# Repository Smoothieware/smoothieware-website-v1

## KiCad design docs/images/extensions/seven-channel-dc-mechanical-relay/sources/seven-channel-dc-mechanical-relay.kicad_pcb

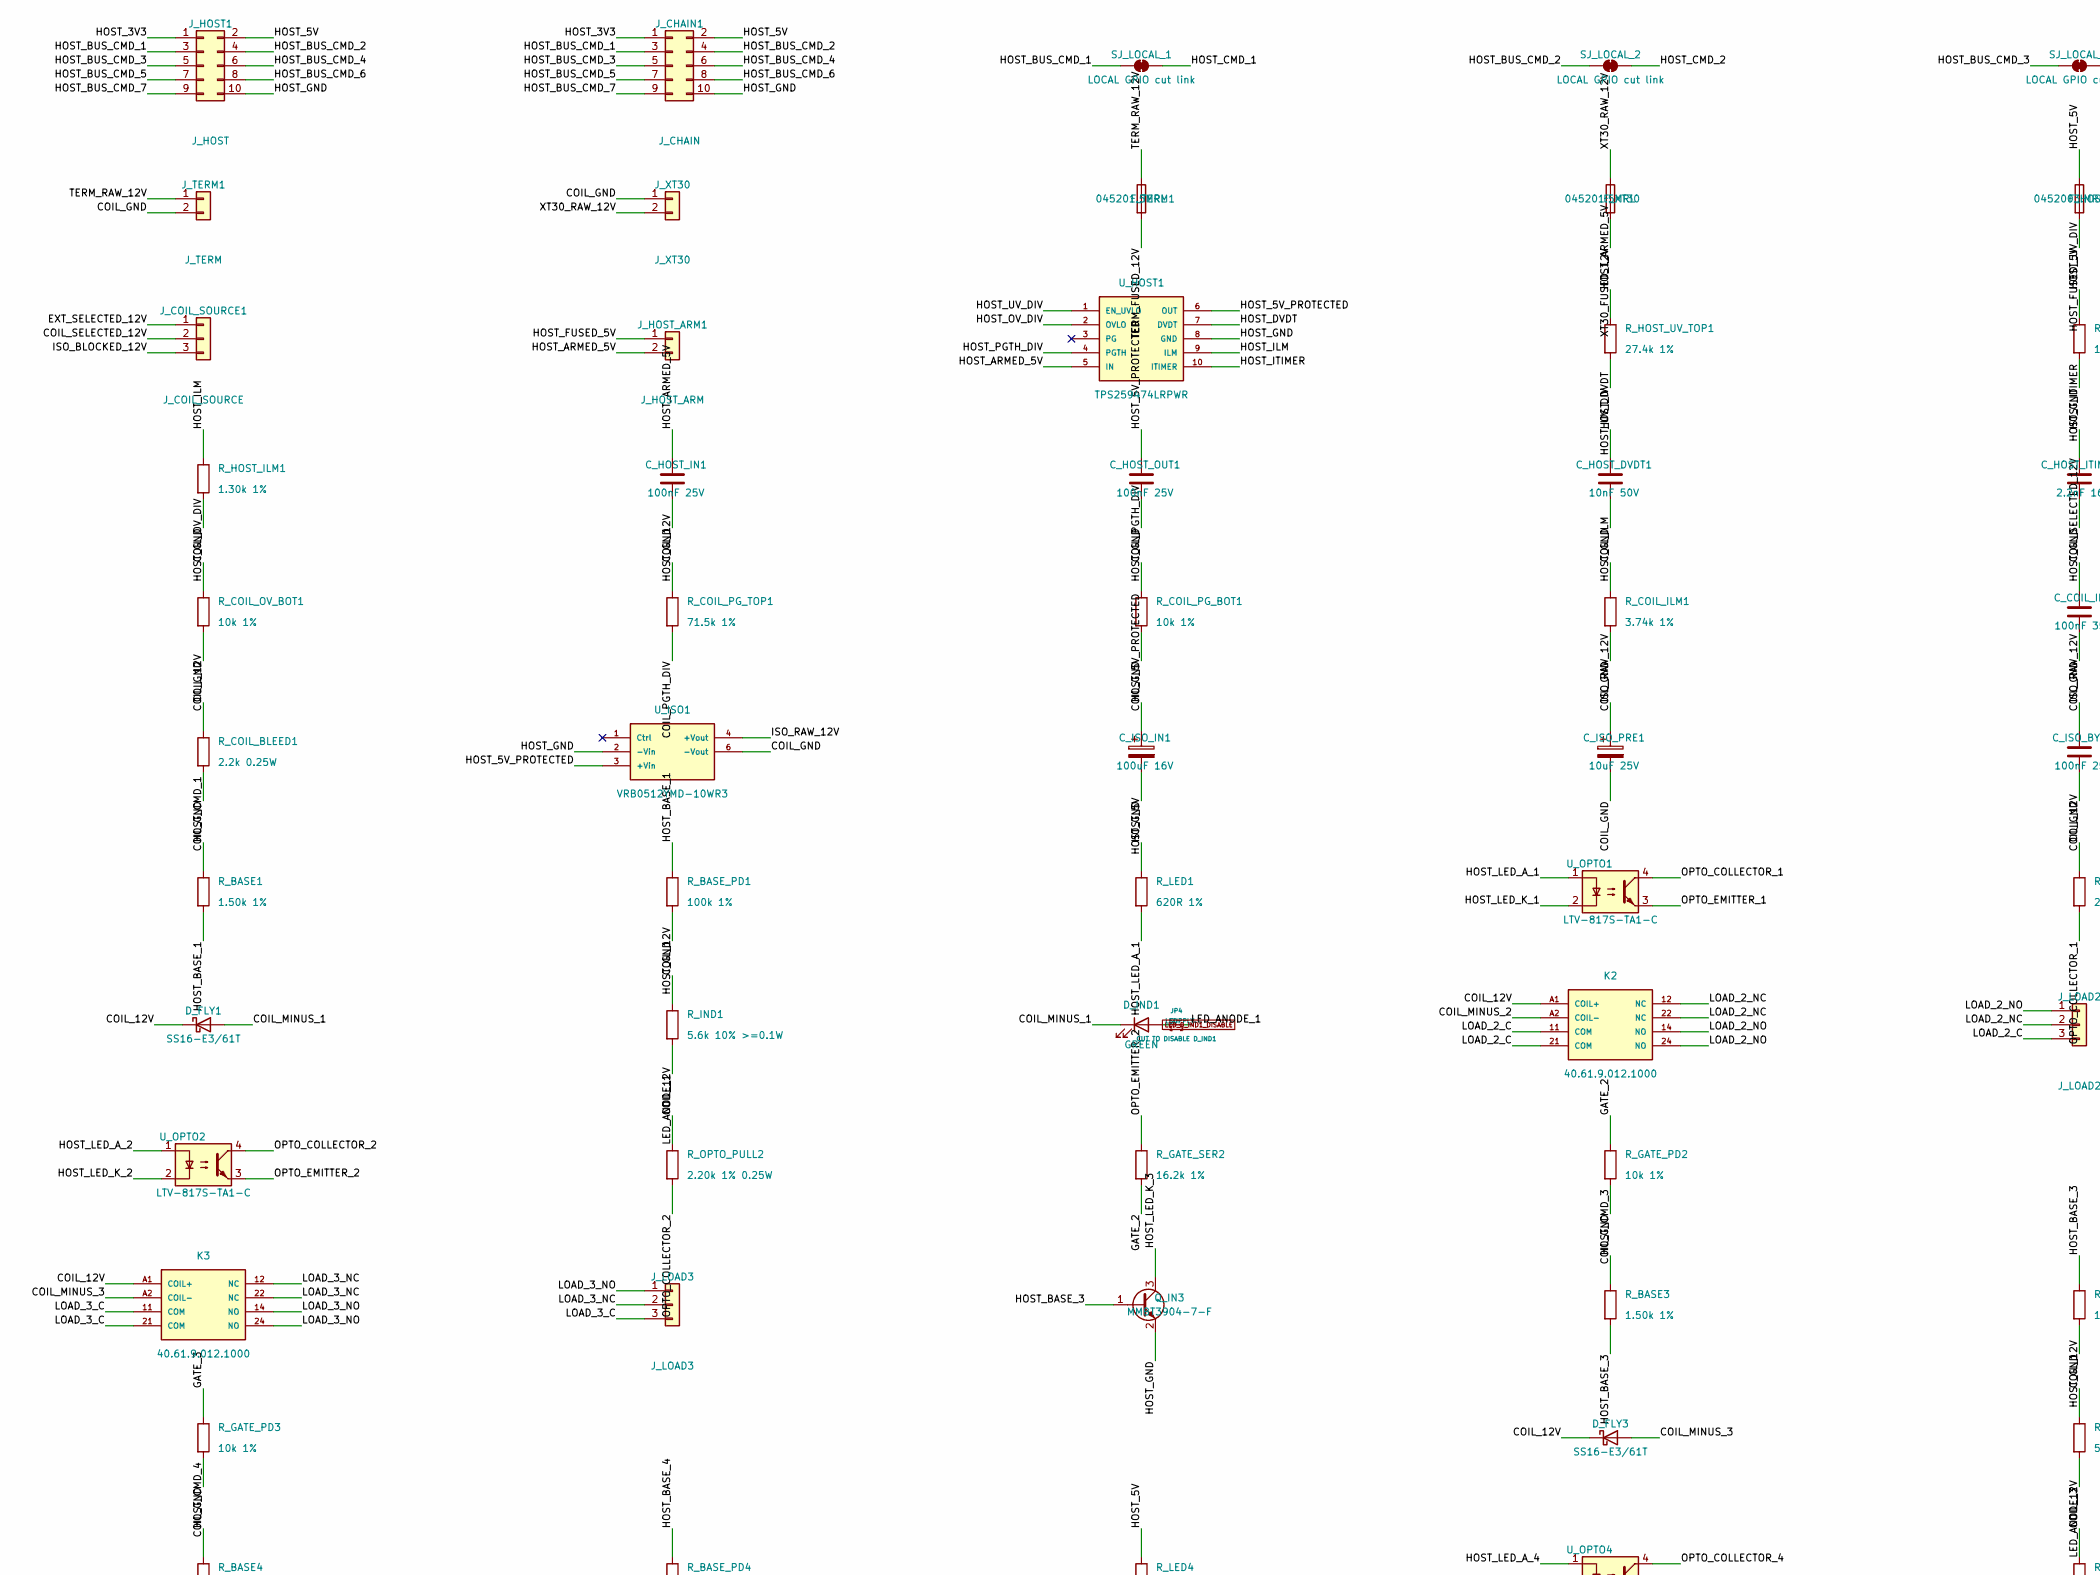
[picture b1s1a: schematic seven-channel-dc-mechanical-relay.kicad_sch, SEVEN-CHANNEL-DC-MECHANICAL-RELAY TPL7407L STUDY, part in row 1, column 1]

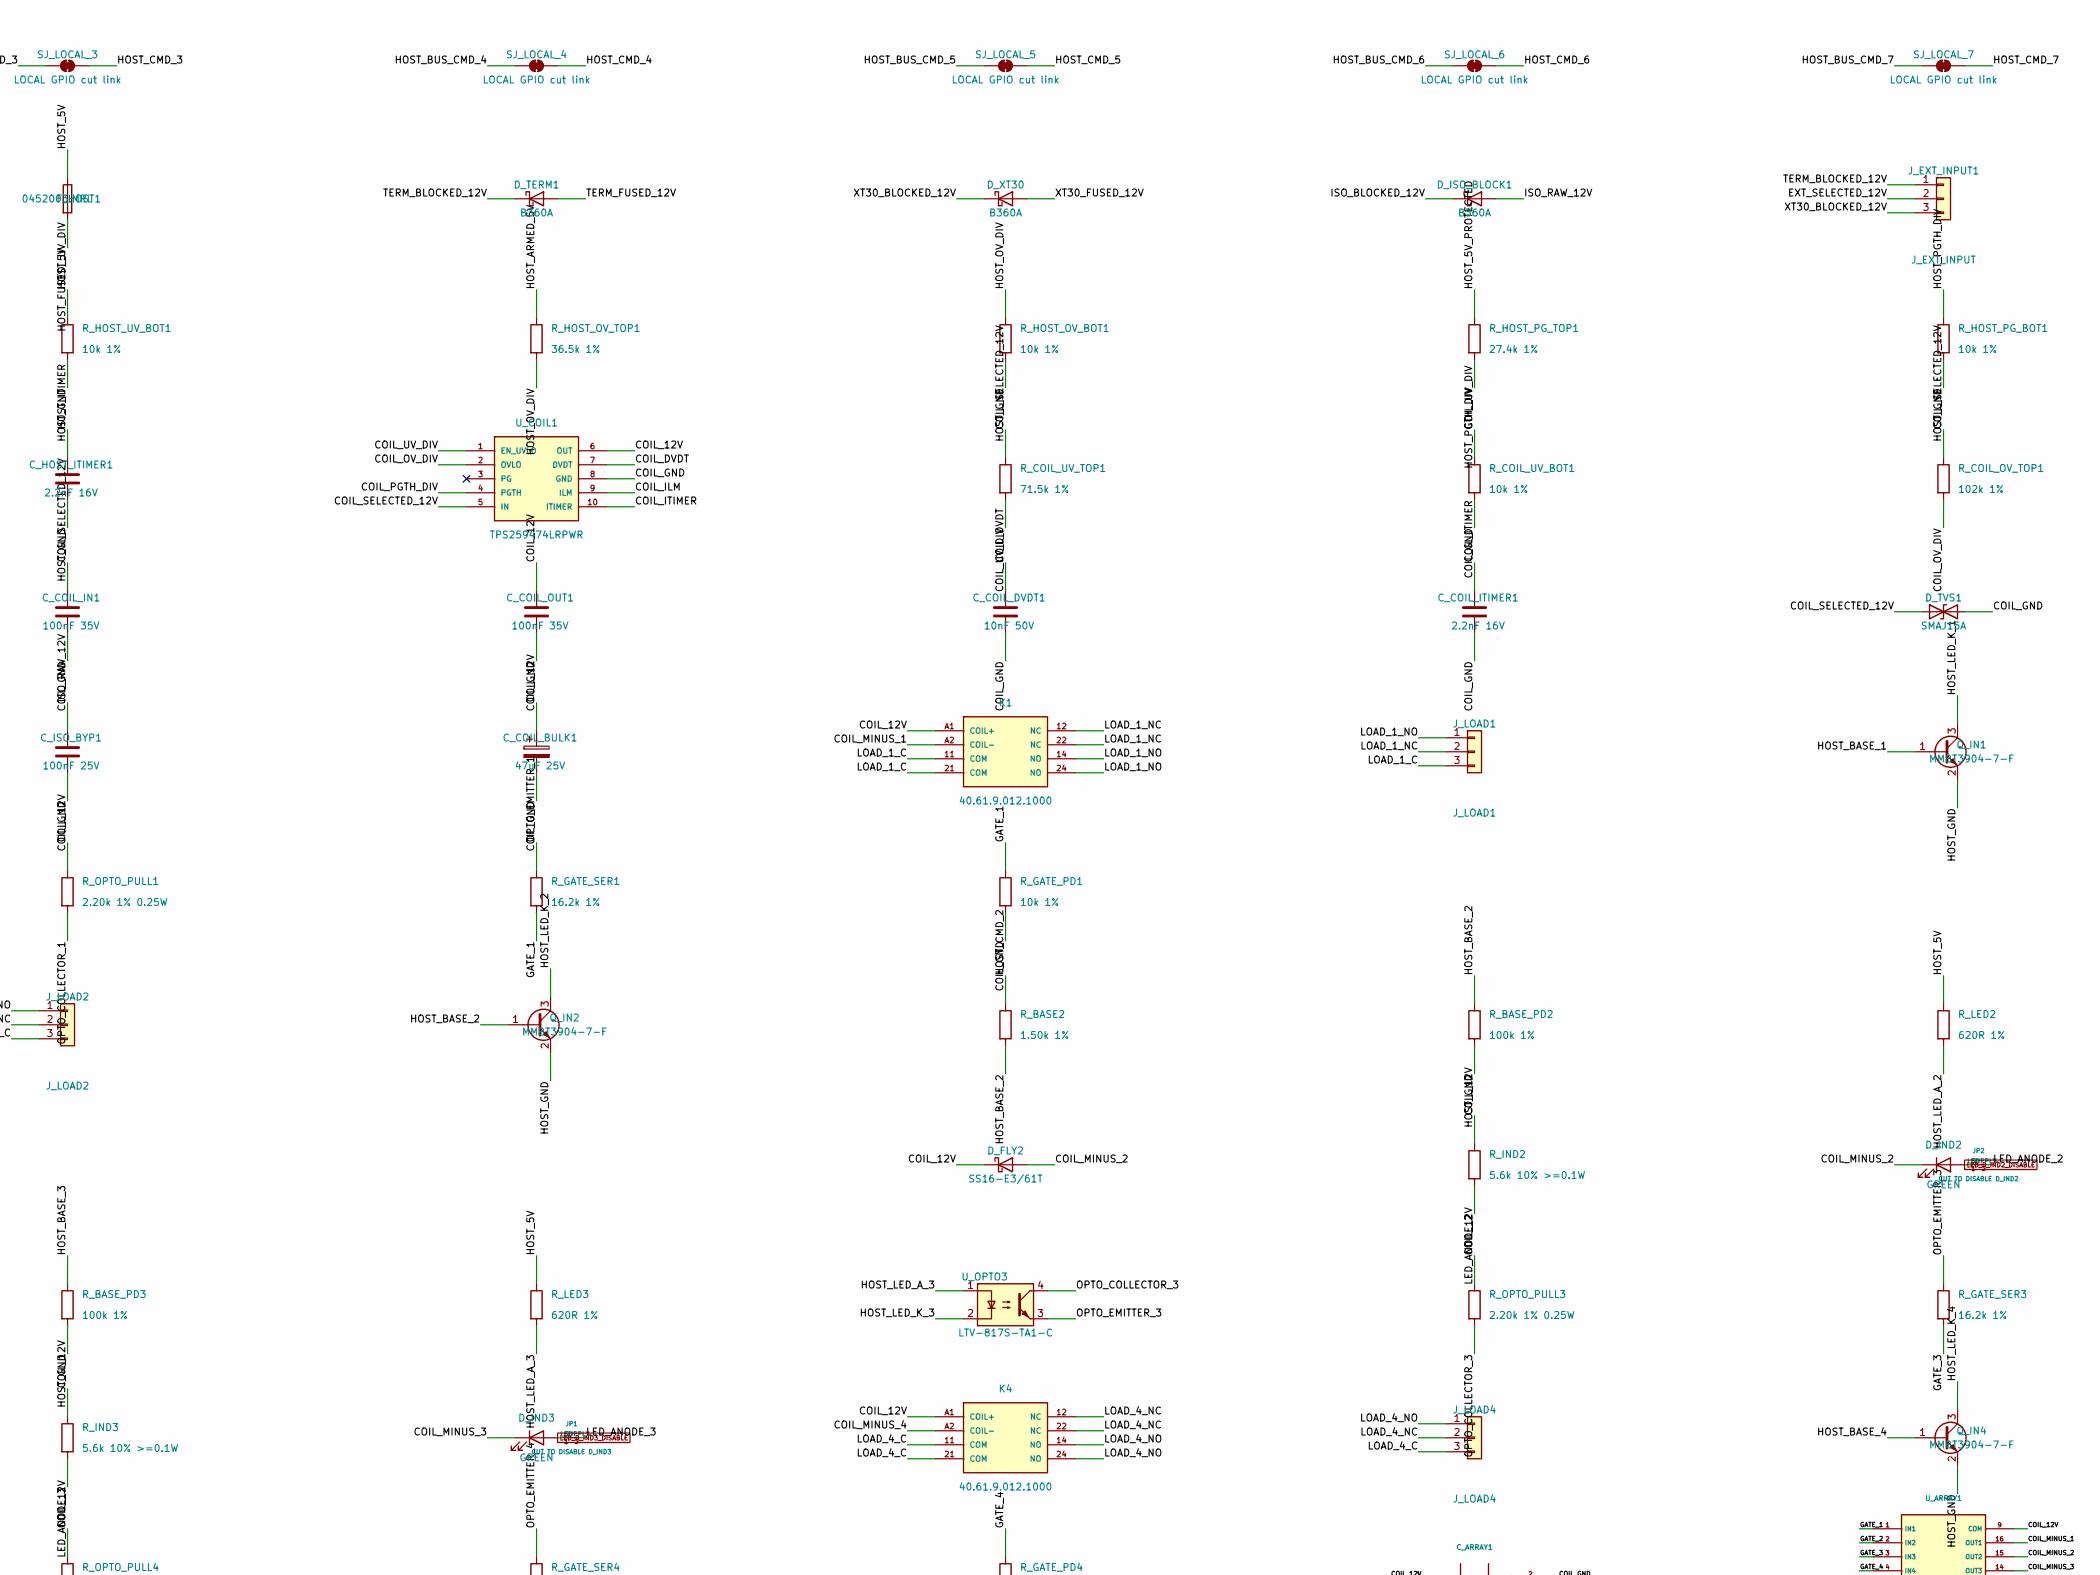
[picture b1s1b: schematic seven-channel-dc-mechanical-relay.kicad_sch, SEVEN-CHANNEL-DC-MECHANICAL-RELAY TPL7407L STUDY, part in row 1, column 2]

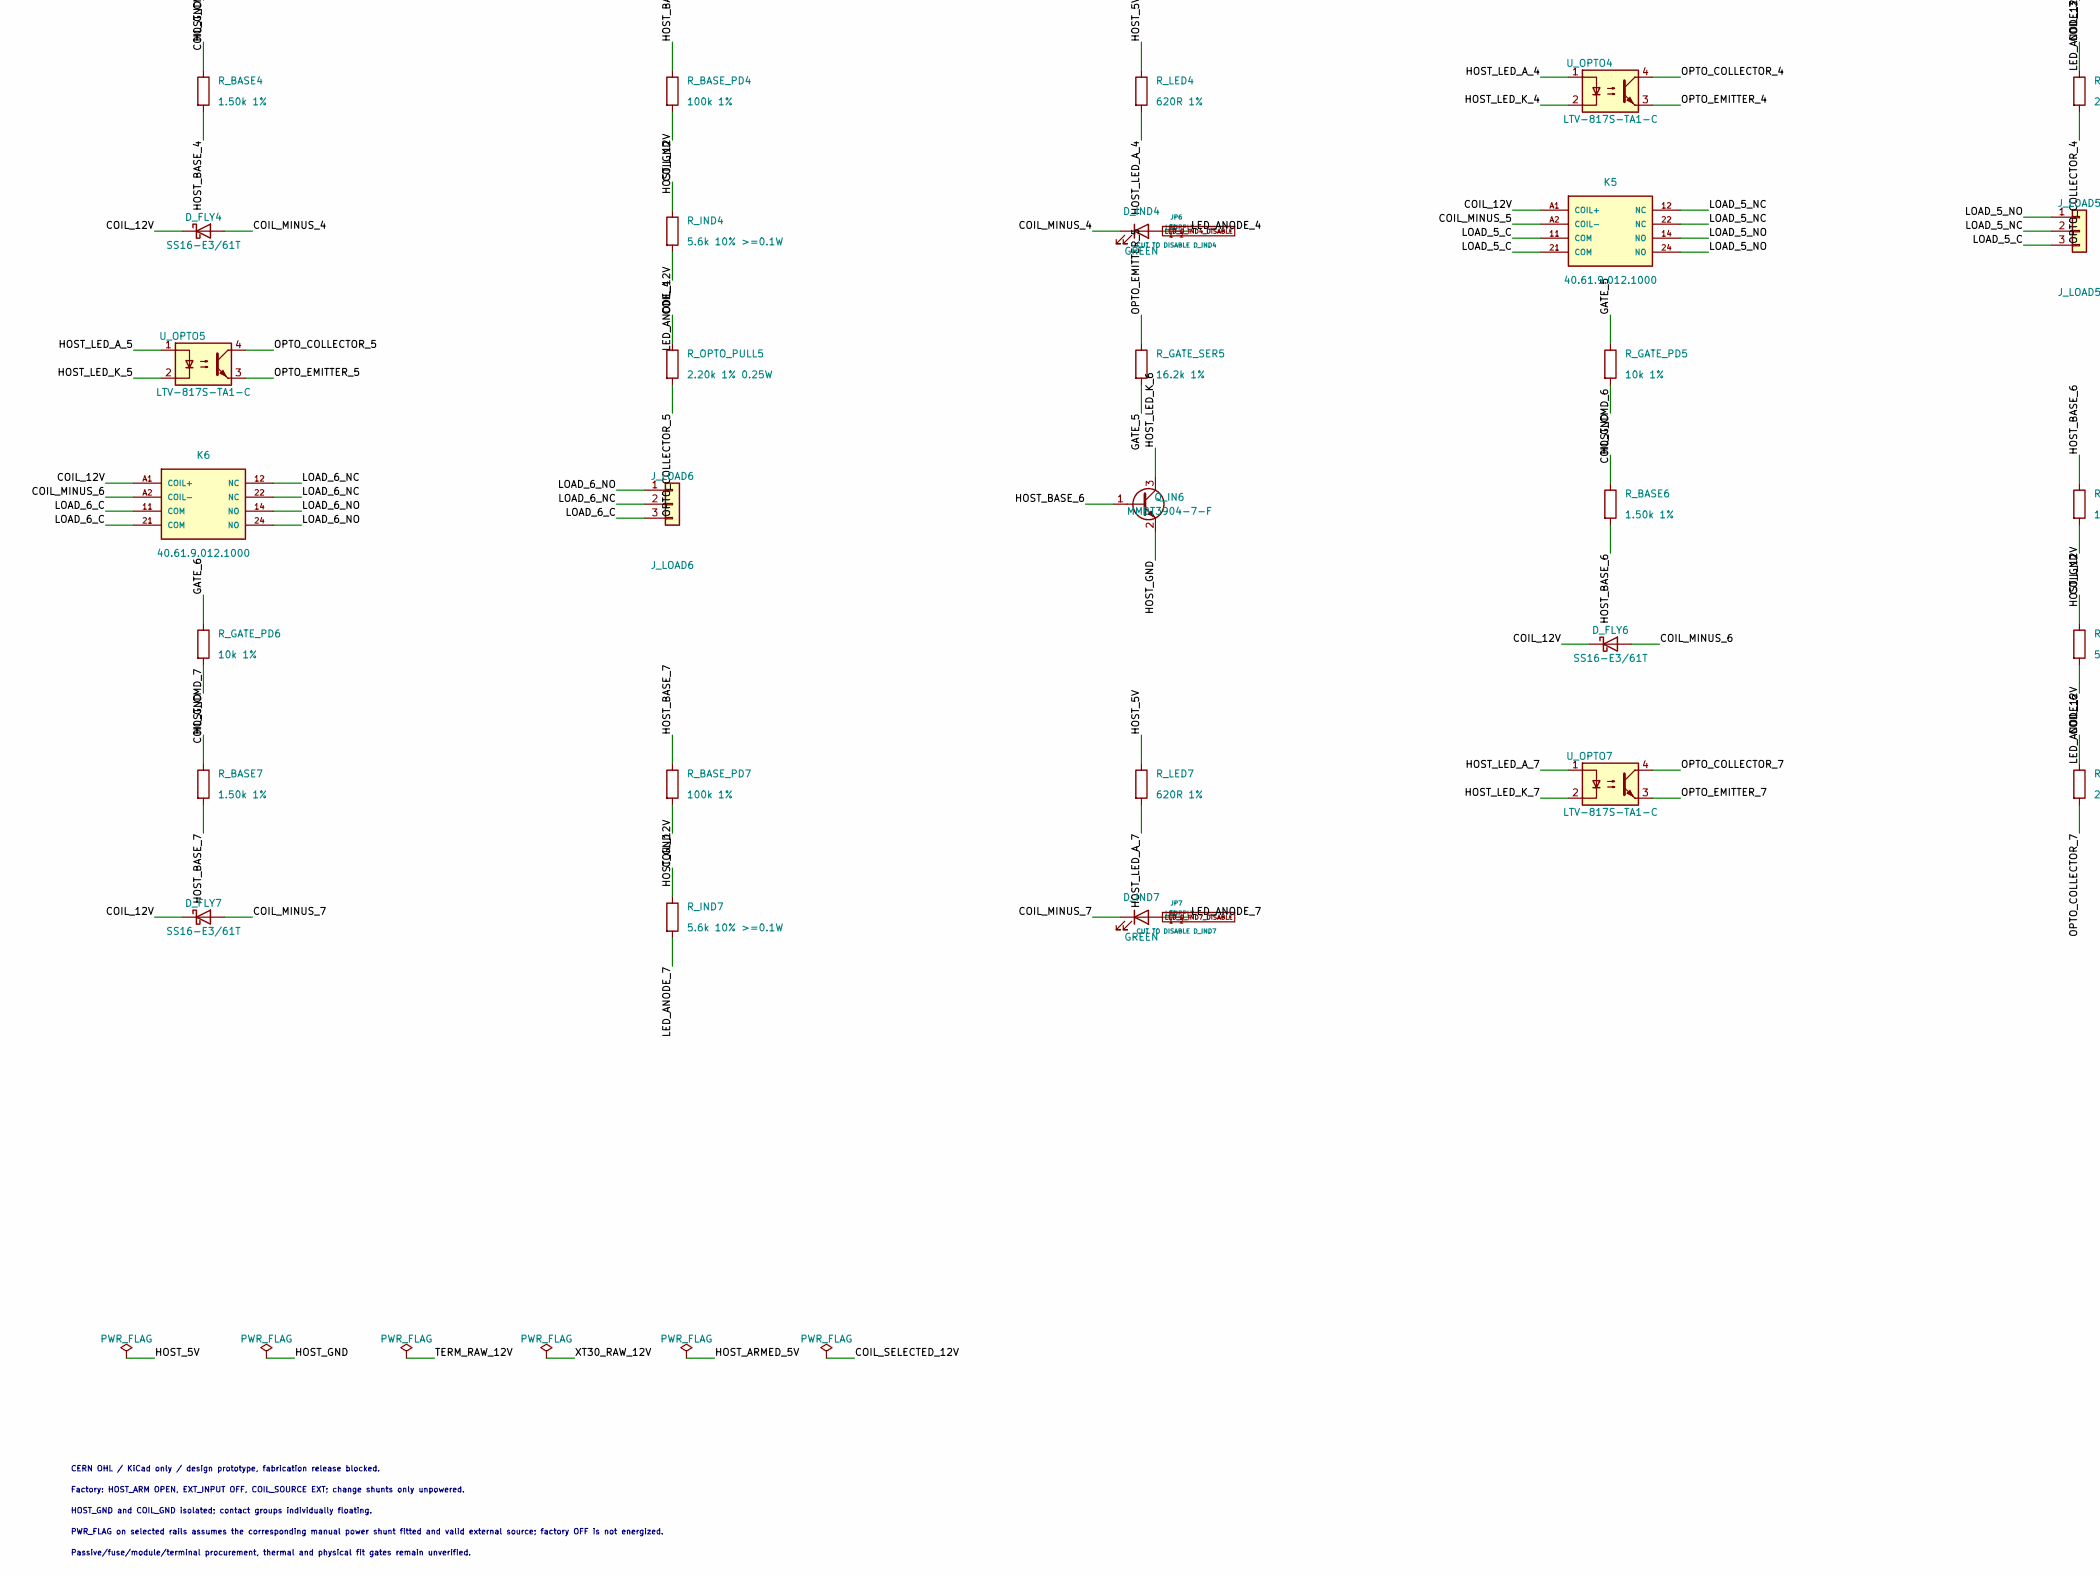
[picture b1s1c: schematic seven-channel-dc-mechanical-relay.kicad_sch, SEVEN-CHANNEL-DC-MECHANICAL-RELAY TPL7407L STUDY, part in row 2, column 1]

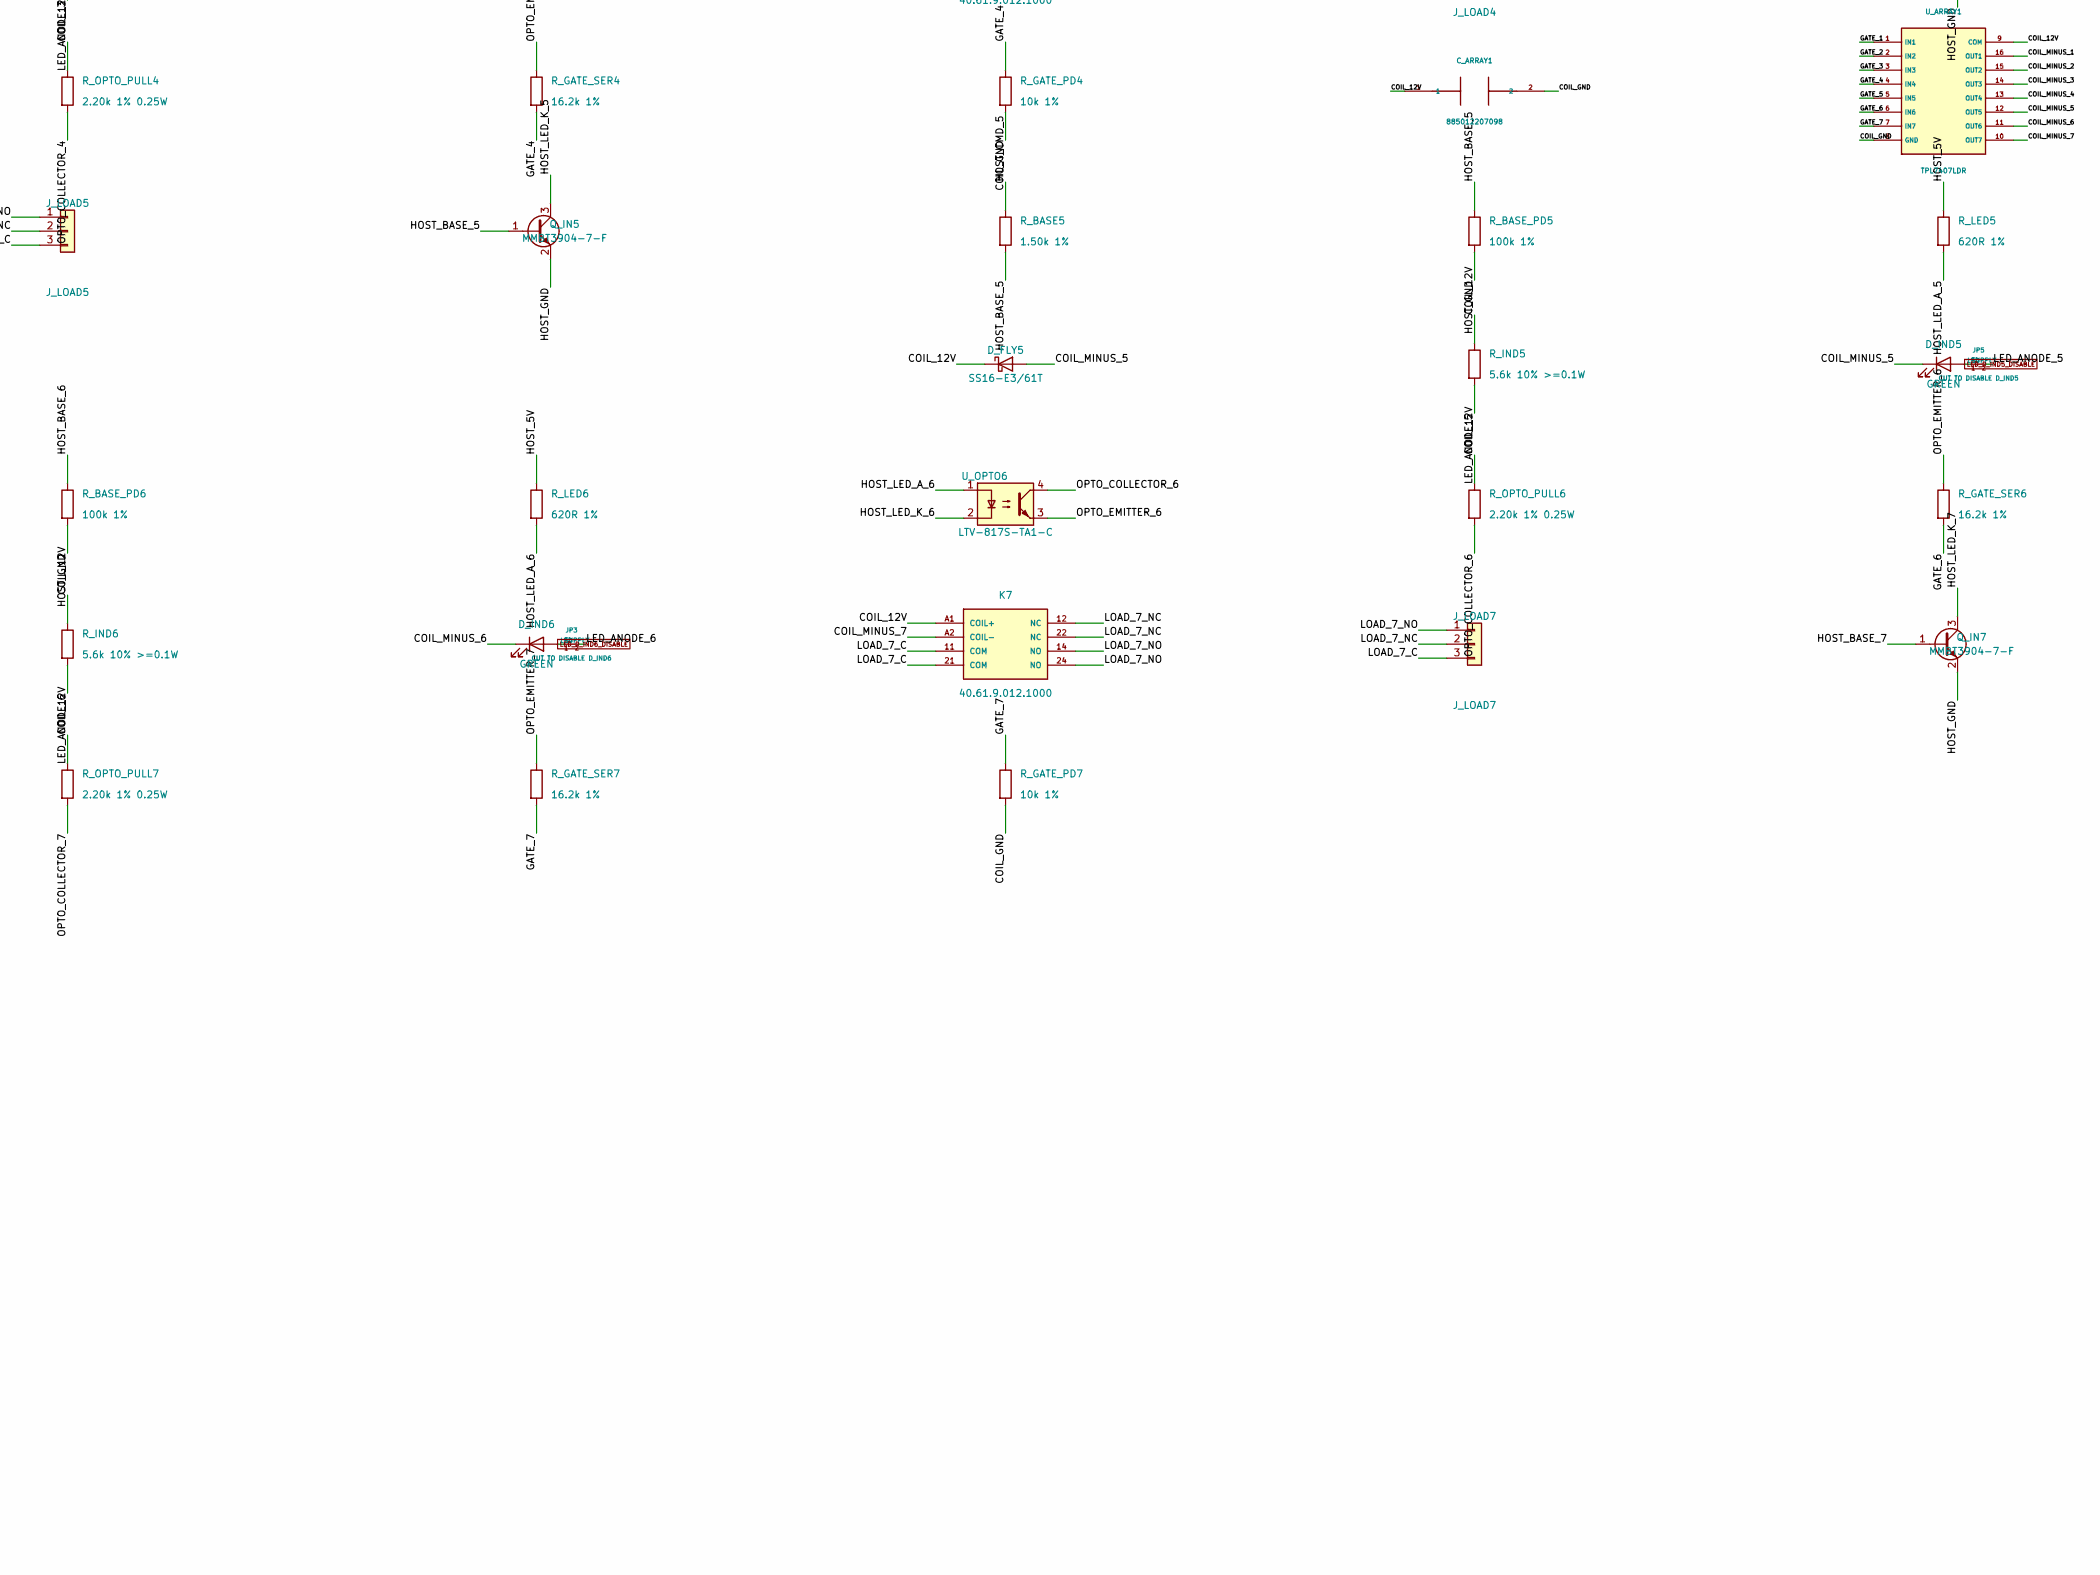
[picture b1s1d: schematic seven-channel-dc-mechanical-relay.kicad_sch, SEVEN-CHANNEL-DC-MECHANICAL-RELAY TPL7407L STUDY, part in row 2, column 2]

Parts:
C_ARRAY1: 885012207098; C_0805_2012Metric
C_COIL_BULK1: 47uF 25V; CP_Radial_D5.0mm_P2.00mm; MPN EEUFR1E470
C_COIL_DVDT1: 10nF 50V; C_0805_2012Metric
C_COIL_IN1: 100nF 35V; C_0805_2012Metric
C_COIL_ITIMER1: 2.2nF 16V; C_0805_2012Metric
C_COIL_OUT1: 100nF 35V; C_0805_2012Metric
C_HOST_DVDT1: 10nF 50V; C_0805_2012Metric
C_HOST_IN1: 100nF 25V; C_0805_2012Metric
C_HOST_ITIMER1: 2.2nF 16V; C_0805_2012Metric
C_HOST_OUT1: 100nF 25V; C_0805_2012Metric
C_ISO_BYP1: 100nF 25V; C_0805_2012Metric
C_ISO_IN1: 100uF 16V; CP_Radial_D5.0mm_P2.00mm; MPN EEUFR1C101
C_ISO_PRE1: 10uF 25V; CP_Radial_D4.0mm_P1.50mm; MPN EEAFC1E100
D_FLY1, D_FLY2, D_FLY3, D_FLY4, D_FLY5, D_FLY6, D_FLY7: SS16-E3/61T; D_SMA; MPN SS16-E3/61T
D_IND1, D_IND2, D_IND3, D_IND4, D_IND5, D_IND6, D_IND7: GREEN; LED_0603_1608Metric; MPN 19-217/GHC-YR1S2/6T
D_ISO_BLOCK1: B360A; D_SMA; MPN B360A-13-F
D_TERM1: B360A; D_SMA; MPN B360A-13-F
D_TVS1: SMAJ15A; D_SMA; MPN SMAJ15A
D_XT30: B360A; D_SMA; MPN B360A-13-F
F_HOST1: 0452003.MRL; Fuse_Littelfuse-NANO2-451_453; MPN 0452003.MRL
F_TERM1: 045201.5MRL; Fuse_Littelfuse-NANO2-451_453; MPN 045201.5MRL
F_XT30: 045201.5MRL; Fuse_Littelfuse-NANO2-451_453; MPN 045201.5MRL
JP1: CUT TO DISABLE D_IND3; SolderJumper-2_P1.3mm_Bridged_RoundedPad1.0x1.5mm
JP2: CUT TO DISABLE D_IND2; SolderJumper-2_P1.3mm_Bridged_RoundedPad1.0x1.5mm
JP3: CUT TO DISABLE D_IND6; SolderJumper-2_P1.3mm_Bridged_RoundedPad1.0x1.5mm
JP4: CUT TO DISABLE D_IND1; SolderJumper-2_P1.3mm_Bridged_RoundedPad1.0x1.5mm
JP5: CUT TO DISABLE D_IND5; SolderJumper-2_P1.3mm_Bridged_RoundedPad1.0x1.5mm
JP6: CUT TO DISABLE D_IND4; SolderJumper-2_P1.3mm_Bridged_RoundedPad1.0x1.5mm
JP7: CUT TO DISABLE D_IND7; SolderJumper-2_P1.3mm_Bridged_RoundedPad1.0x1.5mm
J_CHAIN1: J_CHAIN; Samtec_SHF105_01_L_D_TH; MPN SHF-105-01-L-D-TH
J_COIL_SOURCE1: J_COIL_SOURCE; PinHeader_1x03_P2.54mm_Vertical; MPN TSW-103-07-G-S
J_EXT_INPUT1: J_EXT_INPUT; PinHeader_1x03_P2.54mm_Vertical; MPN TSW-103-07-G-S
J_HOST1: J_HOST; Samtec_SHF105_01_L_D_TH; MPN SHF-105-01-L-D-TH
J_HOST_ARM1: J_HOST_ARM; PinHeader_1x02_P2.54mm_Vertical; MPN TSW-102-07-G-S
J_LOAD1: J_LOAD1; DG302_7.5_03P; MPN DG302-7.5-03P-14-00A(H)
J_LOAD2: J_LOAD2; DG302_7.5_03P; MPN DG302-7.5-03P-14-00A(H)
J_LOAD3: J_LOAD3; DG302_7.5_03P; MPN DG302-7.5-03P-14-00A(H)
J_LOAD4: J_LOAD4; DG302_7.5_03P; MPN DG302-7.5-03P-14-00A(H)
J_LOAD5: J_LOAD5; DG302_7.5_03P; MPN DG302-7.5-03P-14-00A(H)
J_LOAD6: J_LOAD6; DG302_7.5_03P; MPN DG302-7.5-03P-14-00A(H)
J_LOAD7: J_LOAD7; DG302_7.5_03P; MPN DG302-7.5-03P-14-00A(H)
J_TERM1: J_TERM; TerminalBlock_Phoenix_MKDS-1,5-2-5.08_1x02_P5.08mm_Horizont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; MPN 1715721
J_XT30: J_XT30; AMASS_XT30PW-M_1x02_P2.50mm_Horizontal; MPN XT30PW-M30.G.Y
K1, K2, K3, K4, K5, K6, K7: 40.61.9.012.1000; Relay_SPDT_Finder_40.61; MPN 40.61.9.012.1000
Q_IN1, Q_IN2, Q_IN3, Q_IN4, Q_IN5, Q_IN6, Q_IN7: MMBT3904-7-F; SOT-23; MPN MMBT3904-7-F
R_BASE1, R_BASE2, R_BASE3, R_BASE4, R_BASE5, R_BASE6, R_BASE7: 1.50k 1%; R_0805_2012Metric
R_BASE_PD1, R_BASE_PD2, R_BASE_PD3, R_BASE_PD4, R_BASE_PD5, R_BASE_PD6, R_BASE_PD7: 100k 1%; R_0805_2012Metric
R_COIL_BLEED1: 2.2k 0.25W; R_1206_3216Metric
R_COIL_ILM1: 3.74k 1%; R_0805_2012Metric
R_COIL_OV_BOT1: 10k 1%; R_0805_2012Metric
R_COIL_OV_TOP1: 102k 1%; R_0805_2012Metric
R_COIL_PG_BOT1: 10k 1%; R_0805_2012Metric
R_COIL_PG_TOP1: 71.5k 1%; R_0805_2012Metric
R_COIL_UV_BOT1: 10k 1%; R_0805_2012Metric
R_COIL_UV_TOP1: 71.5k 1%; R_0805_2012Metric
R_GATE_PD1, R_GATE_PD2, R_GATE_PD3, R_GATE_PD4, R_GATE_PD5, R_GATE_PD6, R_GATE_PD7: 10k 1%; R_0805_2012Metric
R_GATE_SER1, R_GATE_SER2, R_GATE_SER3, R_GATE_SER4, R_GATE_SER5, R_GATE_SER6, R_GATE_SER7: 16.2k 1%; R_0805_2012Metric
R_HOST_ILM1: 1.30k 1%; R_0805_2012Metric
R_HOST_OV_BOT1: 10k 1%; R_0805_2012Metric
R_HOST_OV_TOP1: 36.5k 1%; R_0805_2012Metric
R_HOST_PG_BOT1: 10k 1%; R_0805_2012Metric
R_HOST_PG_TOP1: 27.4k 1%; R_0805_2012Metric
R_HOST_UV_BOT1: 10k 1%; R_0805_2012Metric
R_HOST_UV_TOP1: 27.4k 1%; R_0805_2012Metric
R_IND1, R_IND2, R_IND3, R_IND4, R_IND5, R_IND6, R_IND7: 5.6k 10% >=0.1W; R_0603_1608Metric
R_LED1, R_LED2, R_LED3, R_LED4, R_LED5, R_LED6, R_LED7: 620R 1%; R_0805_2012Metric
R_OPTO_PULL1, R_OPTO_PULL2, R_OPTO_PULL3, R_OPTO_PULL4, R_OPTO_PULL5, R_OPTO_PULL6, R_OPTO_PULL7: 2.20k 1% 0.25W; R_1206_3216Metric
SJ_LOCAL_1, SJ_LOCAL_2, SJ_LOCAL_3, SJ_LOCAL_4, SJ_LOCAL_5, SJ_LOCAL_6, SJ_LOCAL_7: LOCAL GPIO cut link; SolderJumper-2_P1.3mm_Bridged_Pad1.0x1.5mm
U_ARRAY1: TPL7407LDR; SOIC-16_3.9x9.9mm_P1.27mm
U_COIL1: TPS259474LRPWR; TPS259474_RPW0010A; MPN TPS259474LRPWR
U_HOST1: TPS259474LRPWR; TPS259474_RPW0010A; MPN TPS259474LRPWR
U_ISO1: VRB0512YMD-10WR3; EVISUN_VRB0512YMD_10WR3; MPN VRB0512YMD-10WR3
U_OPTO1, U_OPTO2, U_OPTO3, U_OPTO4, U_OPTO5, U_OPTO6, U_OPTO7: LTV-817S-TA1-C; LTV817S_10.16Span; MPN LTV-817S-TA1-C

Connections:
/COIL_12V: C_ARRAY1.1, C_COIL_BULK1.1, C_COIL_OUT1.1, D_FLY1.1 (K), D_FLY2.1 (K), D_FLY3.1 (K), D_FLY4.1 (K), D_FLY5.1 (K), D_FLY6.1 (K), D_FLY7.1 (K), K1.A1 (COIL+), K2.A1 (COIL+), K3.A1 (COIL+), K4.A1 (COIL+), K5.A1 (COIL+), K6.A1 (COIL+), K7.A1 (COIL+), R_COIL_BLEED1.1, R_COIL_PG_TOP1.1, R_IND1.1, R_IND2.1, R_IND3.1, R_IND4.1, R_IND5.1, R_IND6.1, R_IND7.1, R_OPTO_PULL1.1, R_OPTO_PULL2.1, R_OPTO_PULL3.1, R_OPTO_PULL4.1, R_OPTO_PULL5.1, R_OPTO_PULL6.1, R_OPTO_PULL7.1, U_ARRAY1.9 (COM), U_COIL1.6 (OUT)
/COIL_DVDT: C_COIL_DVDT1.1, U_COIL1.7 (DVDT)
/COIL_GND: C_ARRAY1.2, C_COIL_BULK1.2, C_COIL_DVDT1.2, C_COIL_IN1.2, C_COIL_ITIMER1.2, C_COIL_OUT1.2, C_ISO_BYP1.2, C_ISO_PRE1.2, D_TVS1.2 (A2), J_TERM1.2, J_XT30.1, R_COIL_BLEED1.2, R_COIL_ILM1.2, R_COIL_OV_BOT1.2, R_COIL_PG_BOT1.2, R_COIL_UV_BOT1.2, R_GATE_PD1.2, R_GATE_PD2.2, R_GATE_PD3.2, R_GATE_PD4.2, R_GATE_PD5.2, R_GATE_PD6.2, R_GATE_PD7.2, U_ARRAY1.8 (GND), U_COIL1.8 (GND), U_ISO1.6 (-Vout)
/COIL_ILM: R_COIL_ILM1.1, U_COIL1.9 (ILM)
/COIL_ITIMER: C_COIL_ITIMER1.1, U_COIL1.10 (ITIMER)
/COIL_MINUS_1: D_FLY1.2 (A), D_IND1.1 (K), K1.A2 (COIL-), U_ARRAY1.16 (OUT1)
/COIL_MINUS_2: D_FLY2.2 (A), D_IND2.1 (K), K2.A2 (COIL-), U_ARRAY1.15 (OUT2)
/COIL_MINUS_3: D_FLY3.2 (A), D_IND3.1 (K), K3.A2 (COIL-), U_ARRAY1.14 (OUT3)
/COIL_MINUS_4: D_FLY4.2 (A), D_IND4.1 (K), K4.A2 (COIL-), U_ARRAY1.13 (OUT4)
/COIL_MINUS_5: D_FLY5.2 (A), D_IND5.1 (K), K5.A2 (COIL-), U_ARRAY1.12 (OUT5)
/COIL_MINUS_6: D_FLY6.2 (A), D_IND6.1 (K), K6.A2 (COIL-), U_ARRAY1.11 (OUT6)
/COIL_MINUS_7: D_FLY7.2 (A), D_IND7.1 (K), K7.A2 (COIL-), U_ARRAY1.10 (OUT7)
/COIL_OV_DIV: R_COIL_OV_BOT1.1, R_COIL_OV_TOP1.2, U_COIL1.2 (OVLO)
/COIL_PGTH_DIV: R_COIL_PG_BOT1.1, R_COIL_PG_TOP1.2, U_COIL1.4 (PGTH)
/COIL_SELECTED_12V: C_COIL_IN1.1, D_TVS1.1 (A1), J_COIL_SOURCE1.2, R_COIL_OV_TOP1.1, R_COIL_UV_TOP1.1, U_COIL1.5 (IN)
/COIL_UV_DIV: R_COIL_UV_BOT1.1, R_COIL_UV_TOP1.2, U_COIL1.1 (EN_UVLO)
/EXT_SELECTED_12V: J_COIL_SOURCE1.1, J_EXT_INPUT1.2
/GATE_1: R_GATE_PD1.1, R_GATE_SER1.2, U_ARRAY1.1 (IN1)
/GATE_2: R_GATE_PD2.1, R_GATE_SER2.2, U_ARRAY1.2 (IN2)
/GATE_3: R_GATE_PD3.1, R_GATE_SER3.2, U_ARRAY1.3 (IN3)
/GATE_4: R_GATE_PD4.1, R_GATE_SER4.2, U_ARRAY1.4 (IN4)
/GATE_5: R_GATE_PD5.1, R_GATE_SER5.2, U_ARRAY1.5 (IN5)
/GATE_6: R_GATE_PD6.1, R_GATE_SER6.2, U_ARRAY1.6 (IN6)
/GATE_7: R_GATE_PD7.1, R_GATE_SER7.2, U_ARRAY1.7 (IN7)
/HOST_3V3: J_CHAIN1.1, J_HOST1.1
/HOST_5V: F_HOST1.1, J_CHAIN1.2, J_HOST1.2, R_LED1.1, R_LED2.1, R_LED3.1, R_LED4.1, R_LED5.1, R_LED6.1, R_LED7.1
/HOST_5V_PROTECTED: C_HOST_OUT1.1, C_ISO_IN1.1, R_HOST_PG_TOP1.1, U_HOST1.6 (OUT), U_ISO1.3 (+Vin)
/HOST_ARMED_5V: C_HOST_IN1.1, J_HOST_ARM1.2, R_HOST_OV_TOP1.1, R_HOST_UV_TOP1.1, U_HOST1.5 (IN)
/HOST_BASE_1: Q_IN1.1 (B), R_BASE1.2, R_BASE_PD1.1
/HOST_BASE_2: Q_IN2.1 (B), R_BASE2.2, R_BASE_PD2.1
/HOST_BASE_3: Q_IN3.1 (B), R_BASE3.2, R_BASE_PD3.1
/HOST_BASE_4: Q_IN4.1 (B), R_BASE4.2, R_BASE_PD4.1
/HOST_BASE_5: Q_IN5.1 (B), R_BASE5.2, R_BASE_PD5.1
/HOST_BASE_6: Q_IN6.1 (B), R_BASE6.2, R_BASE_PD6.1
/HOST_BASE_7: Q_IN7.1 (B), R_BASE7.2, R_BASE_PD7.1
/HOST_BUS_CMD_1: J_CHAIN1.3, J_HOST1.3, SJ_LOCAL_1.1 (A)
/HOST_BUS_CMD_2: J_CHAIN1.4, J_HOST1.4, SJ_LOCAL_2.1 (A)
/HOST_BUS_CMD_3: J_CHAIN1.5, J_HOST1.5, SJ_LOCAL_3.1 (A)
/HOST_BUS_CMD_4: J_CHAIN1.6, J_HOST1.6, SJ_LOCAL_4.1 (A)
/HOST_BUS_CMD_5: J_CHAIN1.7, J_HOST1.7, SJ_LOCAL_5.1 (A)
/HOST_BUS_CMD_6: J_CHAIN1.8, J_HOST1.8, SJ_LOCAL_6.1 (A)
/HOST_BUS_CMD_7: J_CHAIN1.9, J_HOST1.9, SJ_LOCAL_7.1 (A)
/HOST_CMD_1: R_BASE1.1, SJ_LOCAL_1.2 (B)
/HOST_CMD_2: R_BASE2.1, SJ_LOCAL_2.2 (B)
/HOST_CMD_3: R_BASE3.1, SJ_LOCAL_3.2 (B)
/HOST_CMD_4: R_BASE4.1, SJ_LOCAL_4.2 (B)
/HOST_CMD_5: R_BASE5.1, SJ_LOCAL_5.2 (B)
/HOST_CMD_6: R_BASE6.1, SJ_LOCAL_6.2 (B)
/HOST_CMD_7: R_BASE7.1, SJ_LOCAL_7.2 (B)
/HOST_DVDT: C_HOST_DVDT1.1, U_HOST1.7 (DVDT)
/HOST_FUSED_5V: F_HOST1.2, J_HOST_ARM1.1
/HOST_GND: C_HOST_DVDT1.2, C_HOST_IN1.2, C_HOST_ITIMER1.2, C_HOST_OUT1.2, C_ISO_IN1.2, J_CHAIN1.10, J_HOST1.10, Q_IN1.2 (E), Q_IN2.2 (E), Q_IN3.2 (E), Q_IN4.2 (E), Q_IN5.2 (E), Q_IN6.2 (E), Q_IN7.2 (E), R_BASE_PD1.2, R_BASE_PD2.2, R_BASE_PD3.2, R_BASE_PD4.2, R_BASE_PD5.2, R_BASE_PD6.2, R_BASE_PD7.2, R_HOST_ILM1.2, R_HOST_OV_BOT1.2, R_HOST_PG_BOT1.2, R_HOST_UV_BOT1.2, U_HOST1.8 (GND), U_ISO1.2 (-Vin)
/HOST_ILM: R_HOST_ILM1.1, U_HOST1.9 (ILM)
/HOST_ITIMER: C_HOST_ITIMER1.1, U_HOST1.10 (ITIMER)
/HOST_LED_A_1: R_LED1.2, U_OPTO1.1
/HOST_LED_A_2: R_LED2.2, U_OPTO2.1
/HOST_LED_A_3: R_LED3.2, U_OPTO3.1
/HOST_LED_A_4: R_LED4.2, U_OPTO4.1
/HOST_LED_A_5: R_LED5.2, U_OPTO5.1
/HOST_LED_A_6: R_LED6.2, U_OPTO6.1
/HOST_LED_A_7: R_LED7.2, U_OPTO7.1
/HOST_LED_K_1: Q_IN1.3 (C), U_OPTO1.2
/HOST_LED_K_2: Q_IN2.3 (C), U_OPTO2.2
/HOST_LED_K_3: Q_IN3.3 (C), U_OPTO3.2
/HOST_LED_K_4: Q_IN4.3 (C), U_OPTO4.2
/HOST_LED_K_5: Q_IN5.3 (C), U_OPTO5.2
/HOST_LED_K_6: Q_IN6.3 (C), U_OPTO6.2
/HOST_LED_K_7: Q_IN7.3 (C), U_OPTO7.2
/HOST_OV_DIV: R_HOST_OV_BOT1.1, R_HOST_OV_TOP1.2, U_HOST1.2 (OVLO)
/HOST_PGTH_DIV: R_HOST_PG_BOT1.1, R_HOST_PG_TOP1.2, U_HOST1.4 (PGTH)
/HOST_UV_DIV: R_HOST_UV_BOT1.1, R_HOST_UV_TOP1.2, U_HOST1.1 (EN_UVLO)
/ISO_BLOCKED_12V: D_ISO_BLOCK1.1 (K), J_COIL_SOURCE1.3
/ISO_RAW_12V: C_ISO_BYP1.1, C_ISO_PRE1.1, D_ISO_BLOCK1.2 (A), U_ISO1.4 (+Vout)
/LED_ANODE_1: JP4.2 (SUPPLY), R_IND1.2
/LED_ANODE_2: JP2.2 (SUPPLY), R_IND2.2
/LED_ANODE_3: JP1.2 (SUPPLY), R_IND3.2
/LED_ANODE_4: JP6.2 (SUPPLY), R_IND4.2
/LED_ANODE_5: JP5.2 (SUPPLY), R_IND5.2
/LED_ANODE_6: JP3.2 (SUPPLY), R_IND6.2
/LED_ANODE_7: JP7.2 (SUPPLY), R_IND7.2
/LOAD_1_C: J_LOAD1.3, K1.11 (COM), K1.21 (COM)
/LOAD_1_NC: J_LOAD1.2, K1.12 (NC), K1.22 (NC)
/LOAD_1_NO: J_LOAD1.1, K1.14 (NO), K1.24 (NO)
/LOAD_2_C: J_LOAD2.3, K2.11 (COM), K2.21 (COM)
/LOAD_2_NC: J_LOAD2.2, K2.12 (NC), K2.22 (NC)
/LOAD_2_NO: J_LOAD2.1, K2.14 (NO), K2.24 (NO)
/LOAD_3_C: J_LOAD3.3, K3.11 (COM), K3.21 (COM)
/LOAD_3_NC: J_LOAD3.2, K3.12 (NC), K3.22 (NC)
/LOAD_3_NO: J_LOAD3.1, K3.14 (NO), K3.24 (NO)
/LOAD_4_C: J_LOAD4.3, K4.11 (COM), K4.21 (COM)
/LOAD_4_NC: J_LOAD4.2, K4.12 (NC), K4.22 (NC)
/LOAD_4_NO: J_LOAD4.1, K4.14 (NO), K4.24 (NO)
/LOAD_5_C: J_LOAD5.3, K5.11 (COM), K5.21 (COM)
/LOAD_5_NC: J_LOAD5.2, K5.12 (NC), K5.22 (NC)
/LOAD_5_NO: J_LOAD5.1, K5.14 (NO), K5.24 (NO)
/LOAD_6_C: J_LOAD6.3, K6.11 (COM), K6.21 (COM)
/LOAD_6_NC: J_LOAD6.2, K6.12 (NC), K6.22 (NC)
/LOAD_6_NO: J_LOAD6.1, K6.14 (NO), K6.24 (NO)
/LOAD_7_C: J_LOAD7.3, K7.11 (COM), K7.21 (COM)
/LOAD_7_NC: J_LOAD7.2, K7.12 (NC), K7.22 (NC)
/LOAD_7_NO: J_LOAD7.1, K7.14 (NO), K7.24 (NO)
/OPTO_COLLECTOR_1: R_OPTO_PULL1.2, U_OPTO1.4
/OPTO_COLLECTOR_2: R_OPTO_PULL2.2, U_OPTO2.4
/OPTO_COLLECTOR_3: R_OPTO_PULL3.2, U_OPTO3.4
/OPTO_COLLECTOR_4: R_OPTO_PULL4.2, U_OPTO4.4
/OPTO_COLLECTOR_5: R_OPTO_PULL5.2, U_OPTO5.4
/OPTO_COLLECTOR_6: R_OPTO_PULL6.2, U_OPTO6.4
/OPTO_COLLECTOR_7: R_OPTO_PULL7.2, U_OPTO7.4
/OPTO_EMITTER_1: R_GATE_SER1.1, U_OPTO1.3
/OPTO_EMITTER_2: R_GATE_SER2.1, U_OPTO2.3
/OPTO_EMITTER_3: R_GATE_SER3.1, U_OPTO3.3
/OPTO_EMITTER_4: R_GATE_SER4.1, U_OPTO4.3
/OPTO_EMITTER_5: R_GATE_SER5.1, U_OPTO5.3
/OPTO_EMITTER_6: R_GATE_SER6.1, U_OPTO6.3
/OPTO_EMITTER_7: R_GATE_SER7.1, U_OPTO7.3
/TERM_BLOCKED_12V: D_TERM1.1 (K), J_EXT_INPUT1.1
/TERM_FUSED_12V: D_TERM1.2 (A), F_TERM1.2
/TERM_RAW_12V: F_TERM1.1, J_TERM1.1
/XT30_BLOCKED_12V: D_XT30.1 (K), J_EXT_INPUT1.3
/XT30_FUSED_12V: D_XT30.2 (A), F_XT30.2
/XT30_RAW_12V: F_XT30.1, J_XT30.2
LED_D_IND1_DISABLE: D_IND1.2 (A), JP4.1 (LED)
LED_D_IND2_DISABLE: D_IND2.2 (A), JP2.1 (LED)
LED_D_IND3_DISABLE: D_IND3.2 (A), JP1.1 (LED)
LED_D_IND4_DISABLE: D_IND4.2 (A), JP6.1 (LED)
LED_D_IND5_DISABLE: D_IND5.2 (A), JP5.1 (LED)
LED_D_IND6_DISABLE: D_IND6.2 (A), JP3.1 (LED)
LED_D_IND7_DISABLE: D_IND7.2 (A), JP7.1 (LED)

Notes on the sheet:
CERN OHL / KiCad only / design prototype, fabrication release blocked.
Factory: HOST_ARM OPEN, EXT_INPUT OFF, COIL_SOURCE EXT; change shunts only unpowered.
HOST_GND and COIL_GND isolated; contact groups individually floating.
PWR_FLAG on selected rails assumes the corresponding manual power shunt fitted and valid external source; factory OFF is not energized.
Passive/fuse/module/terminal procurement, thermal and physical fit gates remain unverified.

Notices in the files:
docs/images/extensions/seven-channel-dc-mechanical-relay/sources/seven-channel-dc-mechanical-relay.kicad_pcb:
CERN OHL / PROTOTYPE
